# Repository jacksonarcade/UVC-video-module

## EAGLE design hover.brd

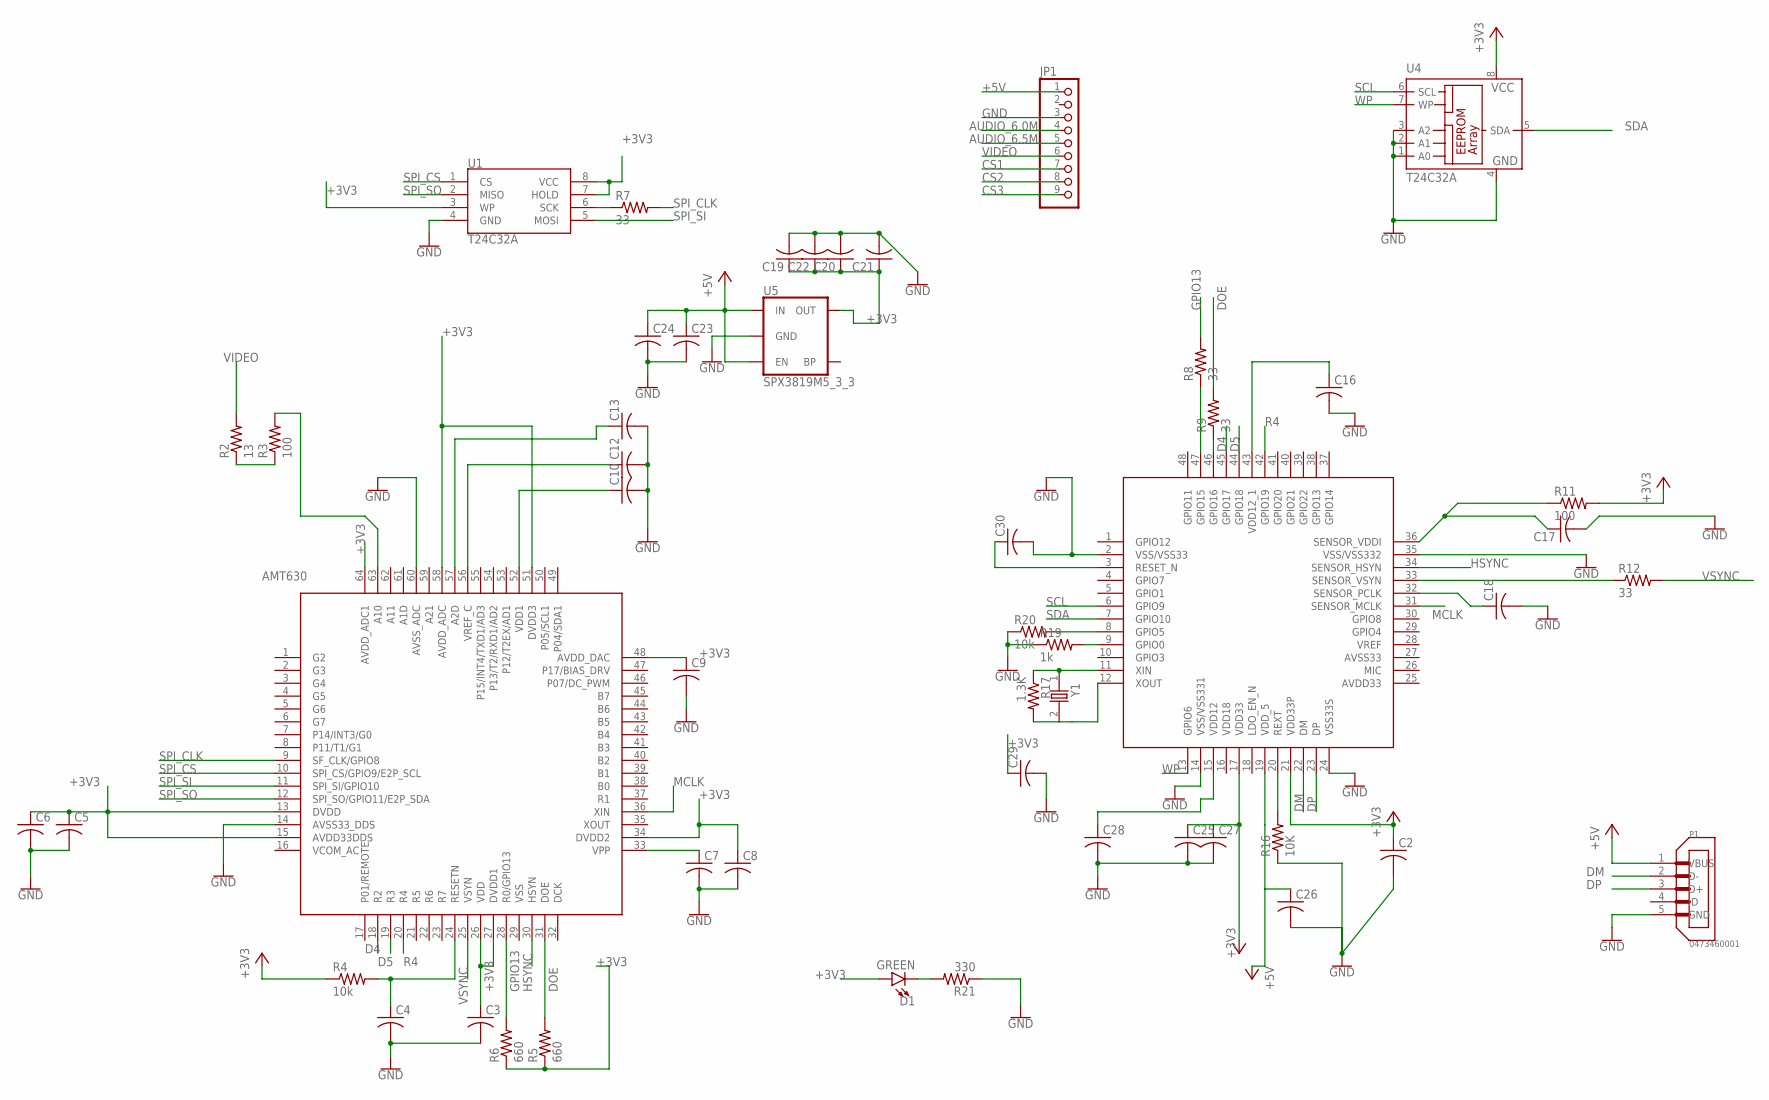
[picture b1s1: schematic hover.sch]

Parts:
C2, C3, C4, C5, C6, C7, C8, C9, C10, C12, C13, C16, C17, C18, C19, C20, C21, C22, C23, C24, C25, C26, C27, C28, C29, C30: C-USC0402; C0402
D1: GREEN; LED-0603
JP1: PINHD-1X9; 1X09-BIG
P1: 0473460001; MOLEX_0473460001
R2: 13; R0402
R3, R11: 100; R0402
R4, R20: 10k; R0402
R5, R6: 660; R0402
R7, R8, R9, R12: 33; R0402
R16: 10K; R0402
R17: 1.3K; R0402
R19: 1k; R0402
R21: 330; R0402
U1: T24C32A; SO08-EIAJ
U2: V399; LQFP48
U3: AMT630; QFP50P1200X1200X160-64N
U4: T24C32A; SOIC127P600X175-8N
U5: SPX3819M5_3_3; SOT23-5
Y1: ABM3-27.000MHZ-B2-T; XTAL500X320X130N

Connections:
+3V3: C2.1, C3.1, C5.1, C6.1, C8.1, C9.1, C19.1, C20.1, C21.1, C22.1, C25.1, C27.1, C29.1, D1.A, R4.1, R5.1, R6.1, R11.2, U1.3 (WP), U1.7 (HOLD), U1.8 (VCC), U2.17 (VDD33), U2.21 (VDD33P), U3.13 (DVDD), U3.15 (AVDD33DDS), U3.26 (VDD), U3.27 (DVDD1), U3.34 (DVDD2), U3.48 (AVDD_DAC), U3.51 (DVDD3), U3.58 (AVDD_ADC), U3.64 (AVDD_ADC1), U4.8 (VCC), U5.5 (OUT)
+5V: C23.1, C24.1, C26.1, JP1.1, P1.1 (VBUS), U2.19 (VDD_5), U5.1 (IN), U5.3 (EN)
AUDIO_6.0M: JP1.4
AUDIO_6.5M: JP1.5
CS1: JP1.7
CS2: JP1.8
CS3: JP1.9
D4: U2.45 (GPIO17), U3.18 (R2)
D5: U2.44 (GPIO18), U3.19 (R3)
DM: P1.2 (D-), U2.22 (DM)
DOE: R5.2, R9.2, U3.31 (DOE)
DP: P1.3 (D+), U2.23 (DP)
GND: C2.2, C3.2, C4.2, C5.2, C6.2, C7.2, C8.2, C9.2, C10.2, C12.2, C13.2, C16.2, C17.2, C18.2, C19.2, C20.2, C21.2, C22.2, C23.2, C24.2, C25.2, C26.2, C27.2, C28.2, C29.2, C30.2, JP1.3, P1.5 (GND), R16.1, R19.1, R20.1, R21.1, U1.4 (GND), U2.2 (VSS/VSS33), U2.14 (VSS/VSS331), U2.24 (VSS33S), U2.35 (VSS/VSS332), U3.14 (AVSS33_DDS), U3.60 (AVSS_ADC), U4.1 (A0), U4.2 (A1), U4.3 (A2), U4.4 (GND), U5.2 (GND)
GPIO13: R6.2, R8.2, U3.28 (R0/GPIO13)
HSYNC: U2.34 (SENSOR_HSYN), U3.30 (HSYN)
MCLK: U2.31 (SENSOR_MCLK), U3.36 (XIN)
unnamed: C4.1, R4.2, U3.24 (RESETN)
unnamed: R2.1, R3.1
unnamed: R8.1, U2.47 (GPIO15)
unnamed: C16.1, U2.43 (VDD12_1)
unnamed: C7.1, U3.33 (VPP)
unnamed: C12.1, U3.56 (VREF_C)
unnamed: C13.1, U3.57 (A2D)
unnamed: C10.1, U3.52 (VDD1)
unnamed: R7.1, U1.6 (SCK)
unnamed: R20.2, U2.8 (GPIO5)
unnamed: R19.2, U2.9 (GPIO0)
unnamed: R16.2, U2.20 (REXT)
unnamed: R17.1, U2.11 (XIN), Y1.1
unnamed: R17.2, U2.12 (XOUT), Y1.2
unnamed: R9.1, U2.46 (GPIO16)
unnamed: R12.1, U2.33 (SENSOR_VSYN)
unnamed: C18.1, U2.32 (SENSOR_PCLK)
unnamed: D1.C, R21.2
unnamed: C30.1, U2.3 (RESET_N)
unnamed: C28.1, U2.15 (VDD12)
unnamed: R3.2, U3.63 (A10)
unnamed: C17.1, R11.1, U2.36 (SENSOR_VDDI)
R4: U2.42 (GPIO19), U3.20 (R4)
SCL: U2.6 (GPIO9), U4.6 (SCL)
SDA: U2.7 (GPIO10), U4.5 (SDA)
SPI_CLK: R7.2, U3.9 (SF_CLK/GPIO8)
SPI_CS: U1.1 (CS), U3.10 (SPI_CS/GPIO9/E2P_SCL)
SPI_SI: U1.5 (MOSI), U3.11 (SPI_SI/GPIO10)
SPI_SO: U1.2 (MISO), U3.12 (SPI_SO/GPIO11/E2P_SDA)
VIDEO: JP1.6, R2.2
VSYNC: R12.2, U3.25 (VSYN)
WP: U2.13 (GPIO6), U4.7 (WP)

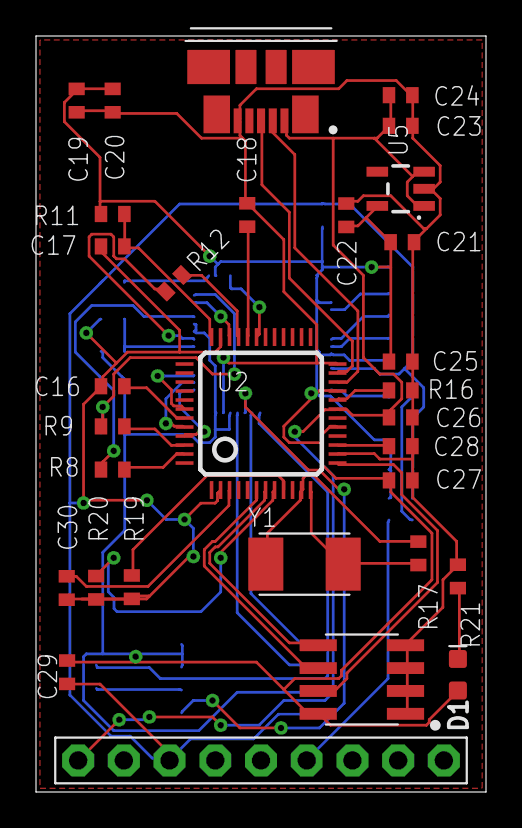
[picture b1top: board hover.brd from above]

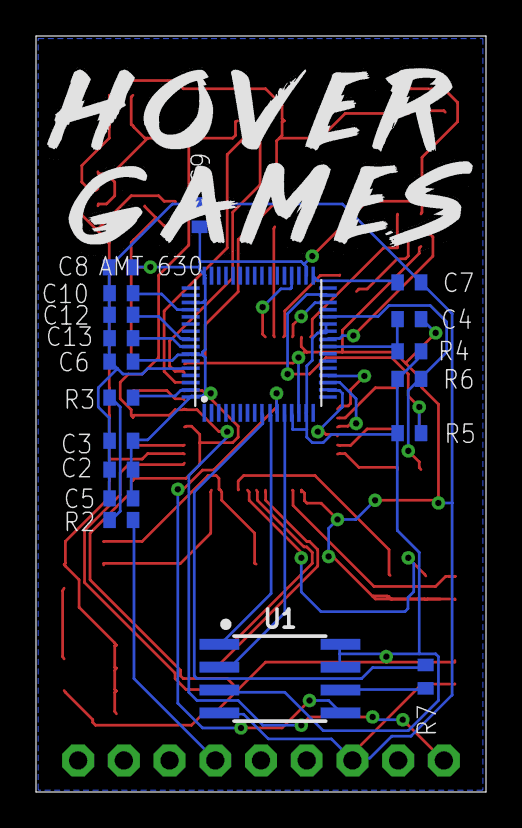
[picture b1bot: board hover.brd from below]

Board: 2 copper layers, 25.0 x 42.0 mm, 50 parts (19 on the bottom side), 43 nets.

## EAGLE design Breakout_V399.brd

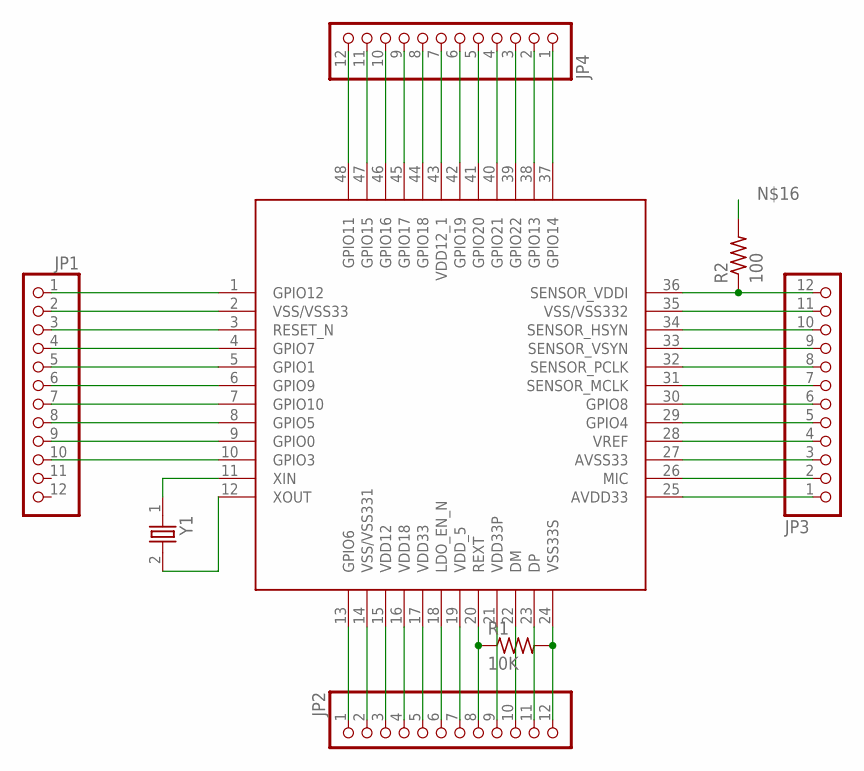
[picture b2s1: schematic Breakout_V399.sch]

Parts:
JP1, JP2, JP3, JP4: PINHD-1X12-CB; 1X12-CB
R1: 10K; R0402
R2: 100; R0402
U1: V399; LQFP48
Y1: ABM3-29.4912MHZ-B2-T; XTAL500X320X130N

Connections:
unnamed: JP1.1, U1.1 (GPIO12)
unnamed: JP1.2, U1.2 (VSS/VSS33)
unnamed: JP1.3, U1.3 (RESET_N)
unnamed: JP1.4, U1.4 (GPIO7)
unnamed: JP1.5, U1.5 (GPIO1)
unnamed: JP1.6, U1.6 (GPIO9)
unnamed: JP1.7, U1.7 (GPIO10)
unnamed: JP1.8, U1.8 (GPIO5)
unnamed: JP1.9, U1.9 (GPIO0)
unnamed: JP1.10, U1.10 (GPIO3)
unnamed: JP2.1, U1.13 (GPIO6)
unnamed: JP2.2, U1.14 (VSS/VSS331)
unnamed: JP2.3, U1.15 (VDD12)
unnamed: JP2.4, U1.16 (VDD18)
unnamed: JP2.5, R2.2, U1.17 (VDD33)
unnamed: JP2.6, U1.18 (LDO_EN_N)
unnamed: JP2.7, U1.19 (VDD_5)
unnamed: JP2.8, R1.1, U1.20 (REXT)
unnamed: JP2.9, U1.21 (VDD33P)
unnamed: JP2.10, U1.22 (DM)
unnamed: JP2.11, U1.23 (DP)
unnamed: JP2.12, R1.2, U1.24 (VSS33S)
unnamed: JP3.1, U1.25 (AVDD33)
unnamed: JP3.2, U1.26 (MIC)
unnamed: JP3.3, U1.27 (AVSS33)
unnamed: JP3.4, U1.28 (VREF)
unnamed: JP3.5, U1.29 (GPIO4)
unnamed: JP3.6, U1.30 (GPIO8)
unnamed: JP3.7, U1.31 (SENSOR_MCLK)
unnamed: JP3.8, U1.32 (SENSOR_PCLK)
unnamed: JP3.9, U1.33 (SENSOR_VSYN)
unnamed: JP3.10, U1.34 (SENSOR_HSYN)
unnamed: JP3.11, U1.35 (VSS/VSS332)
unnamed: JP3.12, R2.1, U1.36 (SENSOR_VDDI)
unnamed: JP4.12, U1.48 (GPIO11)
unnamed: JP4.11, U1.47 (GPIO15)
unnamed: JP4.1, U1.37 (GPIO14)
unnamed: JP4.2, U1.38 (GPIO13)
unnamed: JP4.3, U1.39 (GPIO22)
unnamed: JP4.4, U1.40 (GPIO21)
unnamed: JP4.5, U1.41 (GPIO20)
unnamed: JP4.6, U1.42 (GPIO19)
unnamed: JP4.7, U1.43 (VDD12_1)
unnamed: JP4.8, U1.44 (GPIO18)
unnamed: JP4.9, U1.45 (GPIO17)
unnamed: JP4.10, U1.46 (GPIO16)
unnamed: U1.11 (XIN), Y1.1
unnamed: U1.12 (XOUT), Y1.2

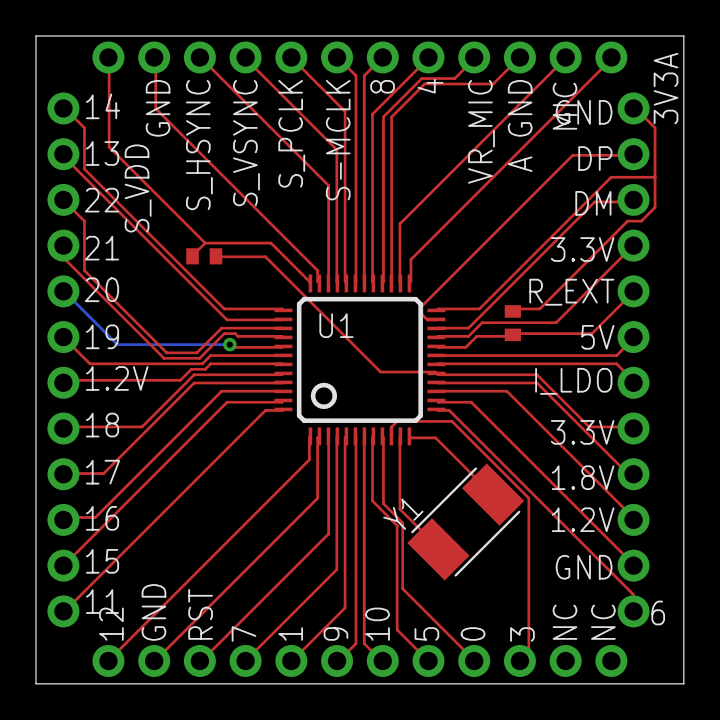
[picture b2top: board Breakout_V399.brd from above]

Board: 2 copper layers, 36.0 x 36.0 mm, 8 parts (0 on the bottom side), 48 nets.

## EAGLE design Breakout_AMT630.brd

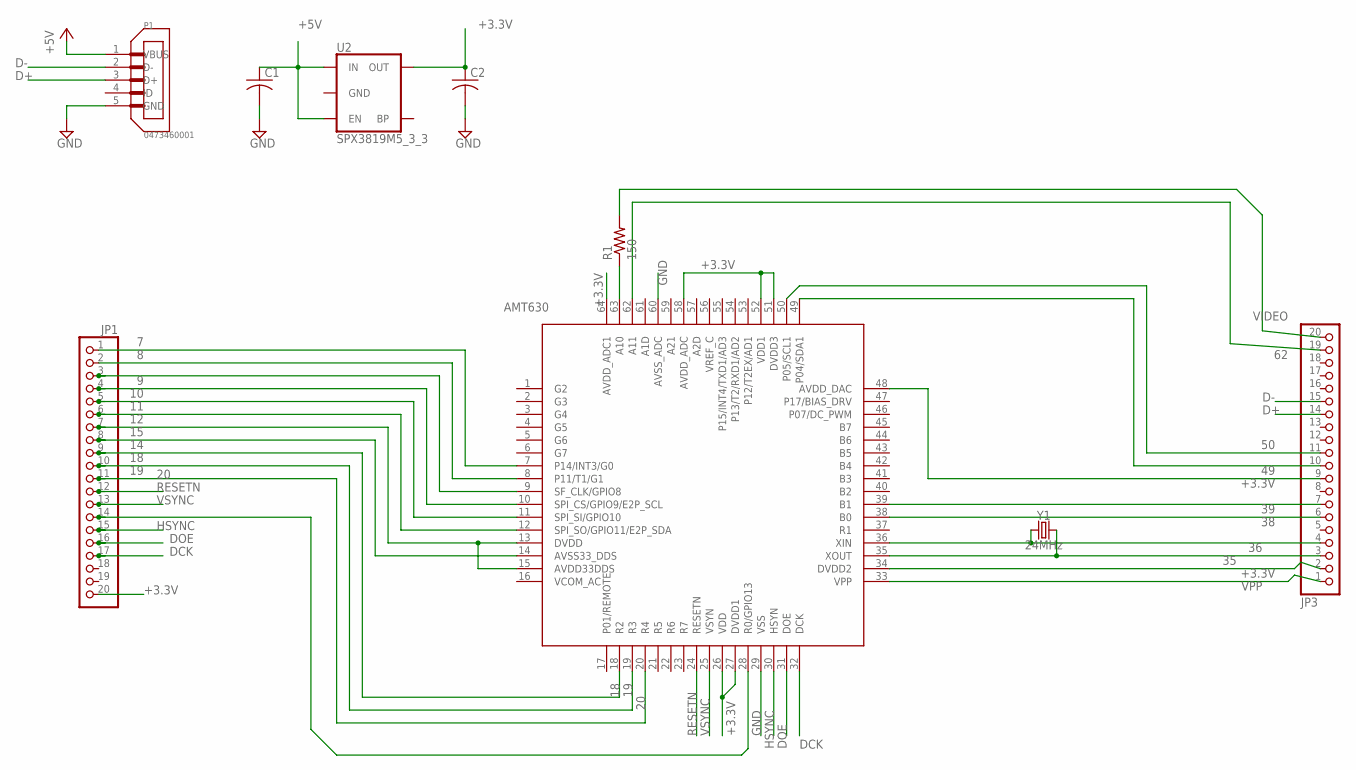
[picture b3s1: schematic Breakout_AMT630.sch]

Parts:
C1, C2: C-USC0402; C0402
JP1, JP3: PINHD-1X20-BIG; 1X20-BIG
P1: 0473460001; MOLEX_0473460001
R1: 150; R0402
U1: AMT630; QFP50P1200X1200X160-64N
U2: SPX3819M5_3_3; SOT23-5
Y1: 24MHz; CRYSTAL-SMD-5X3.2-4PAD

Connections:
7: JP1.1, U1.7 (P14/INT3/G0)
8: JP1.2, U1.8 (P11/T1/G1)
9: JP1.3, U1.9 (SF_CLK/GPIO8)
10: JP1.4, U1.10 (SPI_CS/GPIO9/E2P_SCL)
11: JP1.5, U1.11 (SPI_SI/GPIO10)
12: JP1.6, U1.12 (SPI_SO/GPIO11/E2P_SDA)
14: JP1.8, U1.14 (AVSS33_DDS)
15: JP1.7, U1.13 (DVDD), U1.15 (AVDD33DDS)
18: JP1.9, U1.18 (R2)
19: JP1.10, U1.19 (R3)
20: JP1.11, U1.20 (R4)
28: JP1.14, U1.28 (R0/GPIO13)
35: JP3.3, U1.35 (XOUT), Y1.3 (2)
36: JP3.4, U1.36 (XIN), Y1.1
38: JP3.6, U1.38 (B0)
39: JP3.7, U1.39 (B1)
49: JP3.10, U1.49 (P04/SDA1)
50: JP3.11, U1.50 (P05/SCL1)
62: JP3.19, U1.62 (A11)
+3.3V: C2.1, JP1.20, JP3.2, JP3.9, U1.26 (VDD), U1.27 (DVDD1), U1.34 (DVDD2), U1.48 (AVDD_DAC), U1.51 (DVDD3), U1.52 (VDD1), U1.58 (AVDD_ADC), U1.64 (AVDD_ADC1), U2.5 (OUT)
+5V: C1.1, P1.1 (VBUS), U2.1 (IN), U2.3 (EN)
D+: JP3.14, P1.3 (D+)
D-: JP3.15, P1.2 (D-)
DCK: JP1.17, U1.32 (DCK)
DOE: JP1.16, U1.31 (DOE)
GND: C1.2, C2.2, P1.5 (GND), U1.29 (VSS), U1.60 (AVSS_ADC)
HSYNC: JP1.15, U1.30 (HSYN)
unnamed: R1.1, U1.63 (A10)
RESETN: JP1.12, U1.24 (RESETN)
VIDEO: JP3.20, R1.2
VPP: JP3.1, U1.33 (VPP)
VSYNC: JP1.13, U1.25 (VSYN)

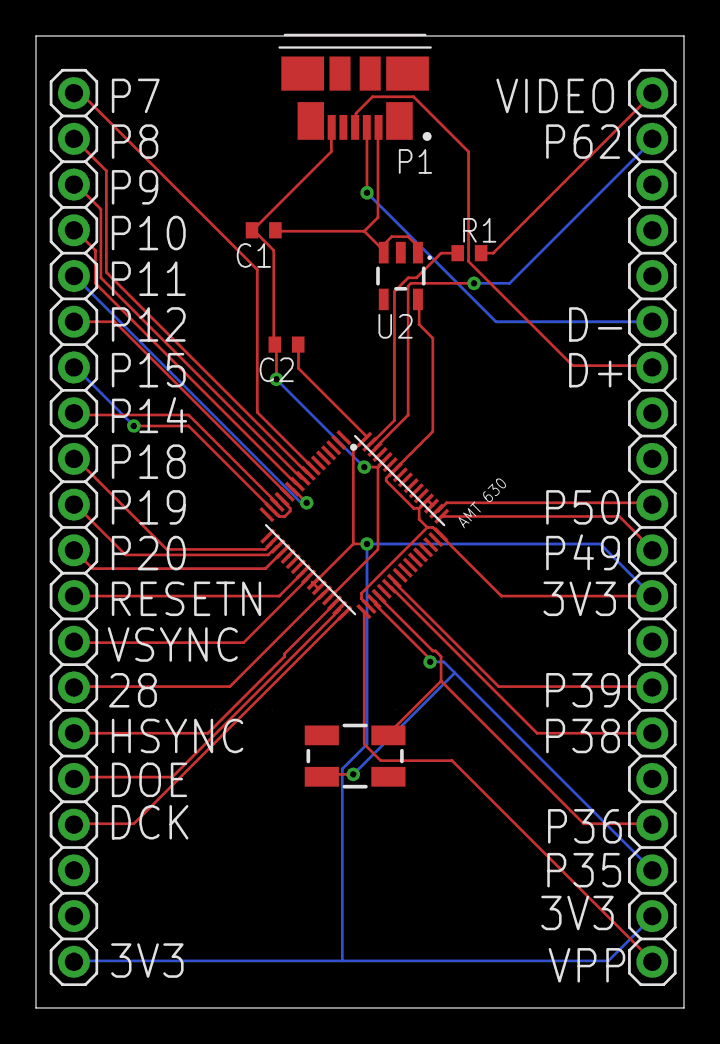
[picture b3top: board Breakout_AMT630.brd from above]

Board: 2 copper layers, 36.0 x 54.0 mm, 9 parts (0 on the bottom side), 32 nets.

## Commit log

2018-02-08 Gerber files include video decoder and USB interface breakout boards

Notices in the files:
parts and their libraries:
SparkFun-Clocks: Licensing: Creative Commons ShareAlike 4.0 International - https://creativecommons.org/licenses/by-sa/4.0
